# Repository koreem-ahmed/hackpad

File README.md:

# hackpad
This is my hackpad, which has a roller, an OLED display, and 9 keys, and of course, the Pi2040. The hackpad is like a control set, which serves a unique purpose for every key. In my case, the first key is opening YouTube, and so on. It acts like a keyboard but for fast and small functions.
# the pcb

# the schematic

# the hole Hack pad

# upper part

# lower part

# the BOM
all the components are in the kit.
the Oled 
9 switches 
9 diodes 
1 XIAO
1 roller 
and 4 rpg light leads.

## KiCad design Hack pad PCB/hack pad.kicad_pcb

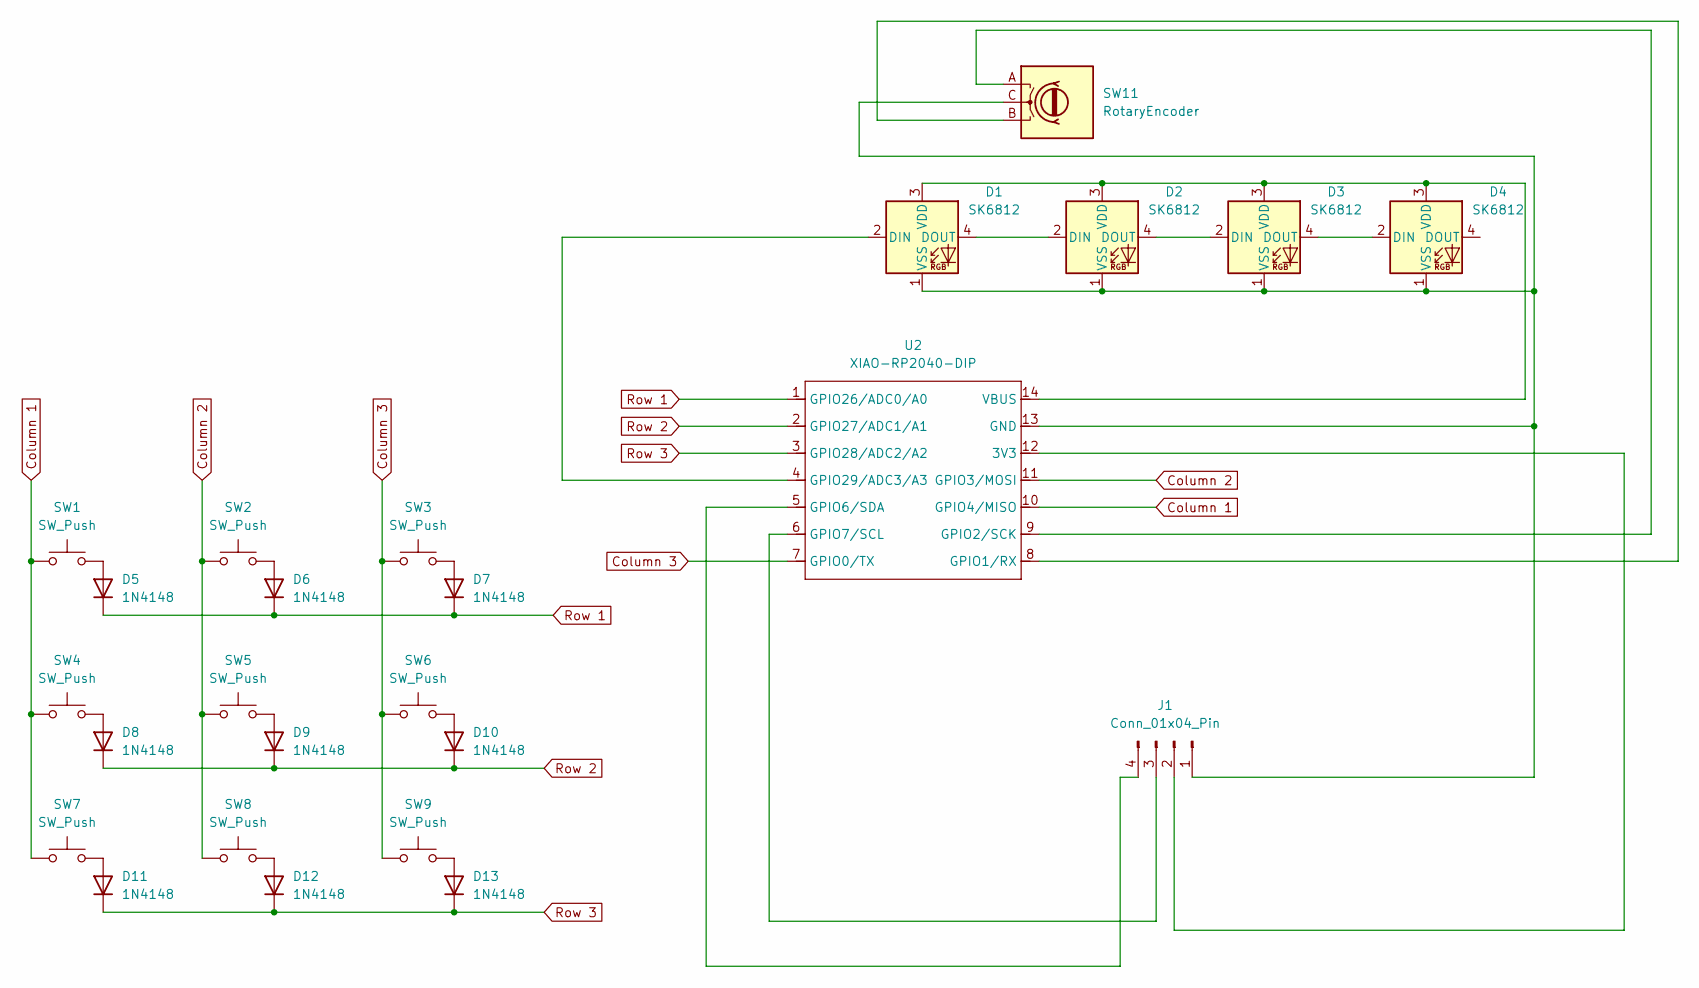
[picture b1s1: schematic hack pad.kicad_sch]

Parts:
D1, D2, D3, D4: SK6812; LED_SK6812MINI_PLCC4_3.5x3.5mm_P1.75mm
D5, D6, D7, D8, D9, D10, D11, D12, D13: 1N4148; D_DO-35_SOD27_P7.62mm_Horizontal
J1: Conn_01x04_Pin; OLED_128x32
SW1, SW2, SW3, SW4, SW5, SW6, SW7, SW8, SW9: SW_Push; Hotswap_MX_1.00u
SW11: RotaryEncoder; Encoder_EC11_MX
U2: XIAO-RP2040-DIP; Seeed_XIAO_RP2040

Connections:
Column 1: SW1.2, SW4.2, SW7.2, U2.10 (GPIO4/MISO)
Column 2: SW2.2, SW5.2, SW8.2, U2.11 (GPIO3/MOSI)
Column 3: SW3.2, SW6.2, SW9.2, U2.7 (GPIO0/TX)
unnamed: D1.2 (DIN), U2.4 (GPIO29/ADC3/A3)
unnamed: D1.4 (DOUT), D2.2 (DIN)
unnamed: D1.3 (VDD), D2.3 (VDD), D3.3 (VDD), D4.3 (VDD), U2.14 (VBUS)
unnamed: D1.1 (VSS), D2.1 (VSS), D3.1 (VSS), D4.1 (VSS), J1.1, SW11.C, U2.13 (GND)
unnamed: D2.4 (DOUT), D3.2 (DIN)
unnamed: D3.4 (DOUT), D4.2 (DIN)
unnamed: D5.2 (A), SW1.1
unnamed: D6.2 (A), SW2.1
unnamed: D7.2 (A), SW3.1
unnamed: D8.2 (A), SW4.1
unnamed: D9.2 (A), SW5.1
unnamed: D10.2 (A), SW6.1
unnamed: D11.2 (A), SW7.1
unnamed: D12.2 (A), SW8.1
unnamed: D13.2 (A), SW9.1
unnamed: J1.2, U2.12 (3V3)
unnamed: J1.3, U2.6 (GPIO7/SCL)
unnamed: J1.4, U2.5 (GPIO6/SDA)
unnamed: SW11.B, U2.8 (GPIO1/RX)
unnamed: SW11.A, U2.9 (GPIO2/SCK)
Row 1: D5.1 (K), D6.1 (K), D7.1 (K), U2.1 (GPIO26/ADC0/A0)
Row 2: D8.1 (K), D9.1 (K), D10.1 (K), U2.2 (GPIO27/ADC1/A1)
Row 3: D11.1 (K), D12.1 (K), D13.1 (K), U2.3 (GPIO28/ADC2/A2)

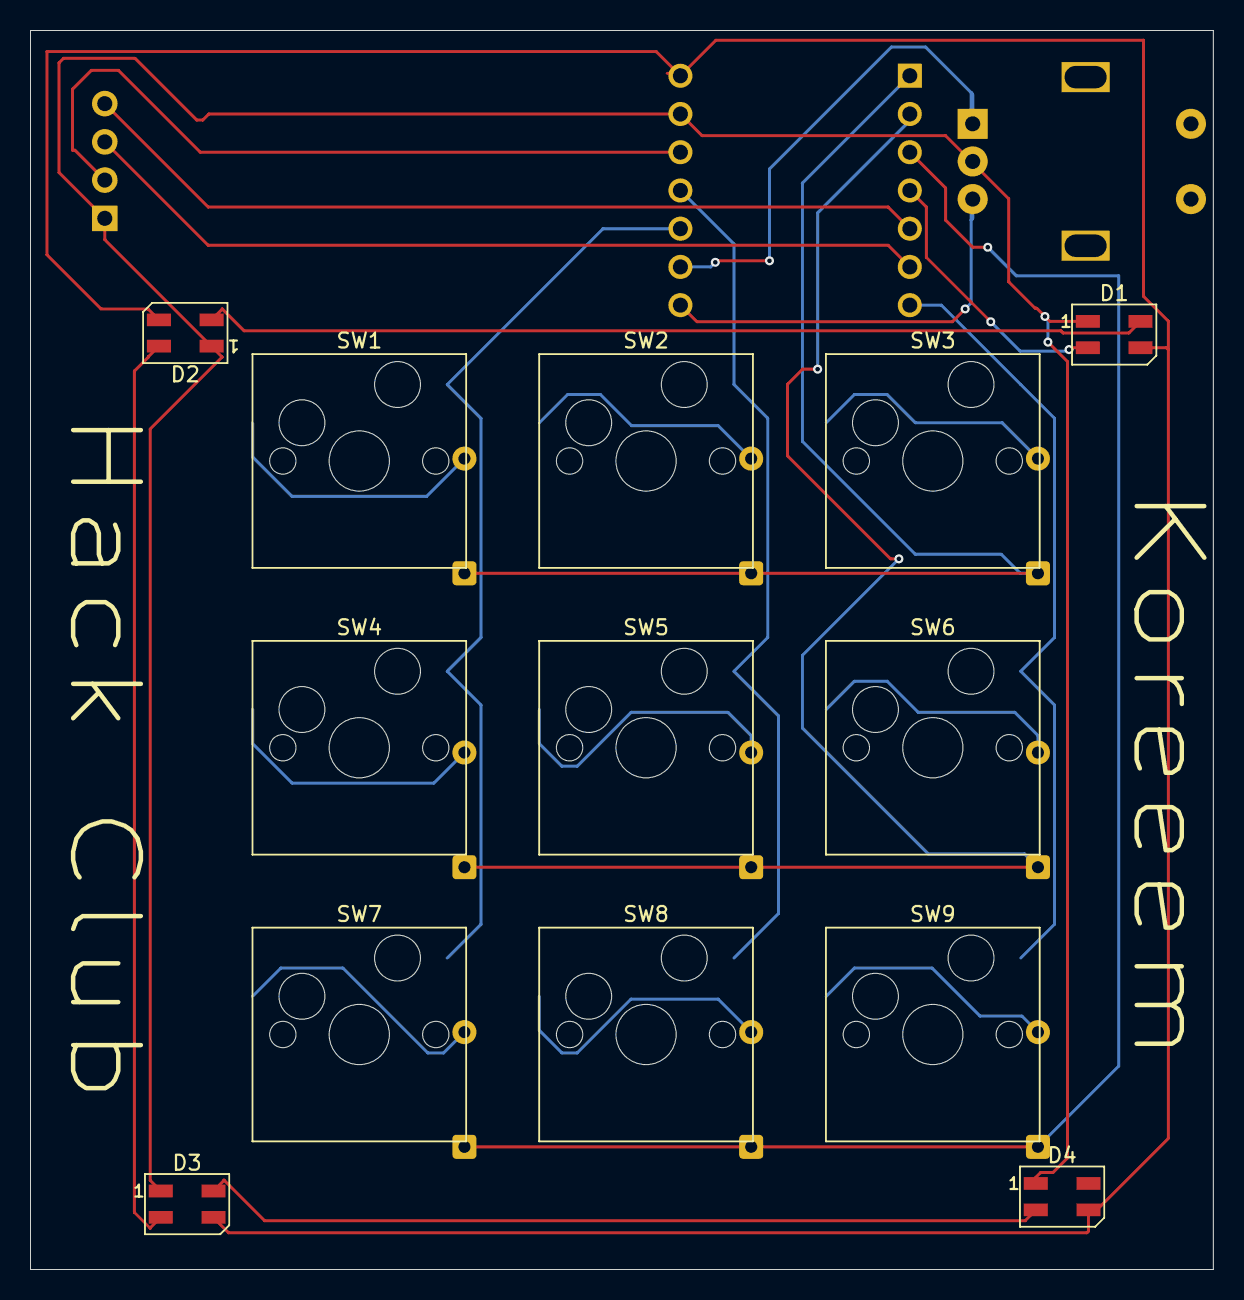
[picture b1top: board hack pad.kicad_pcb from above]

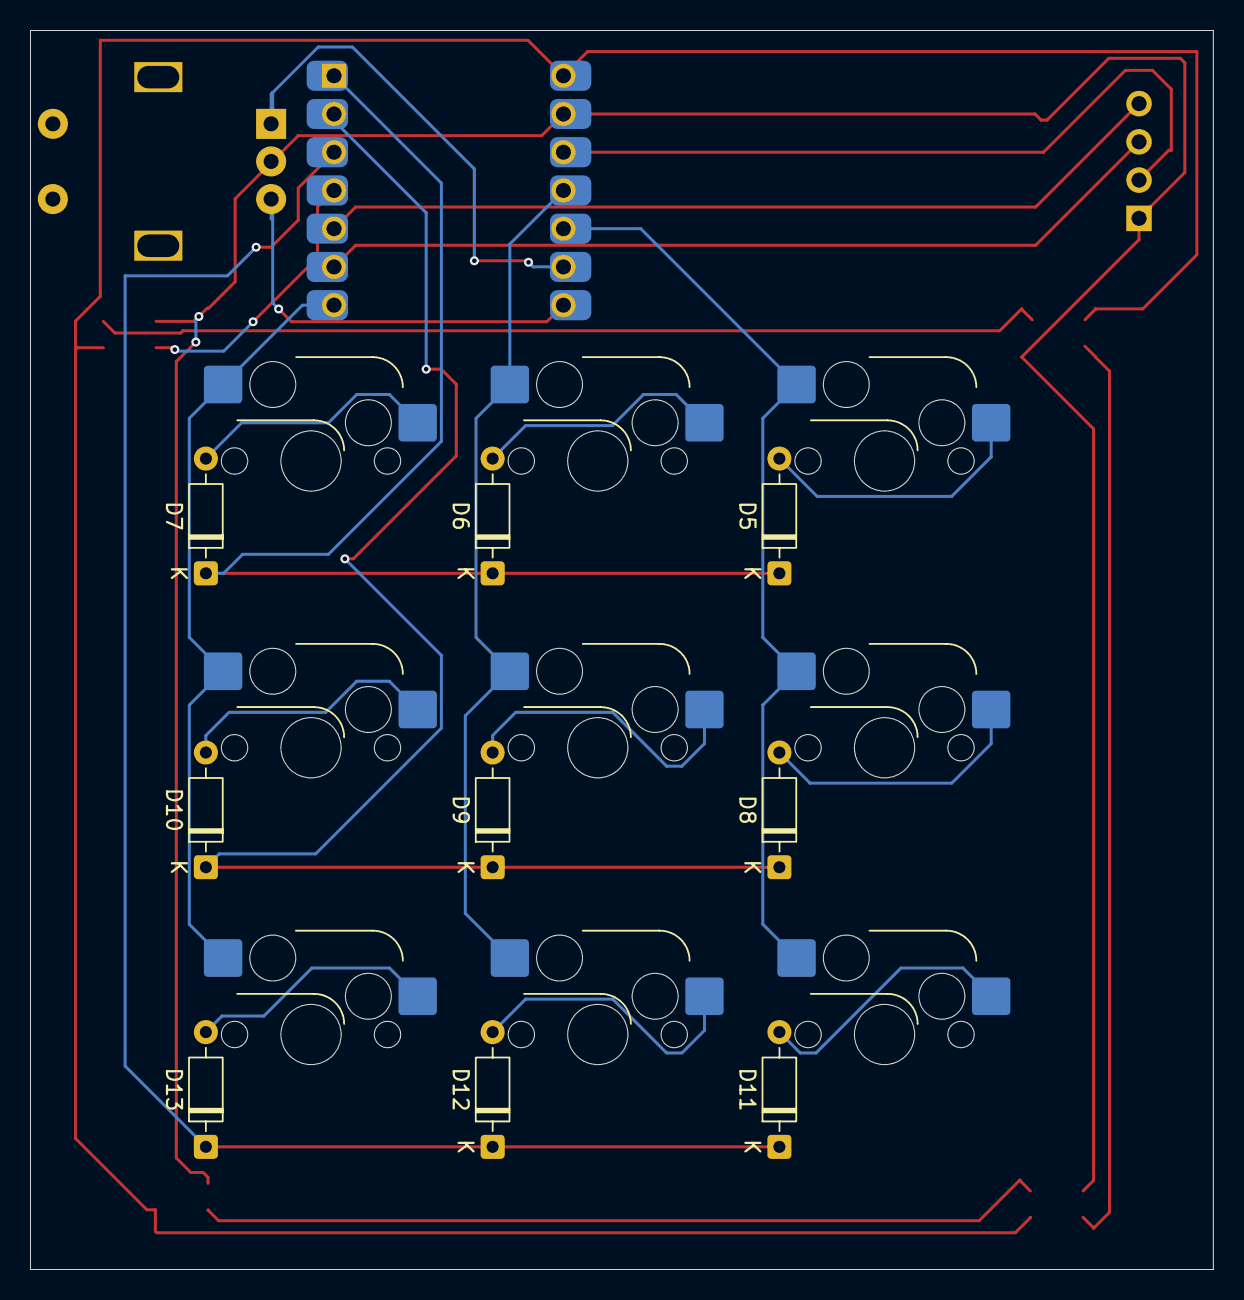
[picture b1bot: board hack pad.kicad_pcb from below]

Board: 2 copper layers, 78.6 x 82.3 mm, 25 parts (10 on the bottom side), 26 nets.

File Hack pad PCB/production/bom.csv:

Designator,Footprint,Quantity,Value,LCSC Part #
"D1, D2, D3, D4",LED_SK6812_PLCC4_5.0x5.0mm_P3.2mm,4,SK6812,
"D10, D11, D12, D13, D5, D6, D7, D8, D9",D_DO-35_SOD27_P7.62mm_Horizontal,9,1N4148,
J1,SSD1306-0.91-OLED-4pin-128x32,1,Conn_01x04_Pin,
"SW1, SW2, SW3, SW4, SW5, SW6, SW7, SW8, SW9",SW_Cherry_MX_1.00u_PCB,9,SW_Push,
SW11,RotaryEncoder_Alps_EC11E_Vertical_H20mm_CircularMountingHoles,1,RotaryEncoder,
U2,XIAO-RP2040-DIP,1,XIAO-RP2040-DIP,

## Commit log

2025-06-27 Update README.md
    this is my hack pad it has a roller a oled display 4 rgp leds and 9 keys
